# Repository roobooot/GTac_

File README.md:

# A Biomimetic Design of HeteroGeneous Tactile Sensor (GTac) Providing Normal and Shear Force Feedback

## General Introduction

This repo includes:

<ul>
  <li>the <a href="https://github.com/roobooot/GTac_/tree/main/software">code</a> 
    <ul>
      <li><a href="https://github.com/roobooot/GTac_/tree/main/software/arduino_lib">low-level controller</a> of GTac-Hand and GTac-Gripper</li>
      <li><a href="https://github.com/roobooot/GTac_/tree/main/software/GTac_Sensor">collecting data from GTac</a></li>
      <li>algorithms used for case study in papers, for instance, learning-based ECS recognition, handover controller, force-closed grasping, etc.</li>
    </ul>
</li>
  <li>the <a href="https://github.com/roobooot/GTac_/tree/main/hardware">hardware design</a>.
    <ul>
      <li><a href="https://github.com/roobooot/GTac_/tree/main/hardware/PCB%20design">PCB design</a> of GTac, reading-out boards, and the motors driving boards.</li>
      <li><a href="https://github.com/roobooot/GTac_/tree/main/hardware/Mechanical%20design">mechenical design</a> (CAD models)</li>
    </ul>
    </li>
</ul>

## Published Works

### GTac: A Biomimetic Tactile Sensor with Skin-like Heterogeneous Force Feedback for Robots

This paper is to introduce the design, fabrication methods, and force sensing principles of GTac.
For more information, please check out our paper below.

Z. Lu, X. Gao and H. Yu, "GTac: A Biomimetic Tactile Sensor With Skin-Like Heterogeneous Force Feedback for Robots," in IEEE Sensors Journal, vol. 22, no. 14, pp. 14491-14500, 15 July15, 2022, doi: 10.1109/JSEN.2022.3181128.

#### Video
<!------>
<p align="center">

</p>

## Contact Information
If you have any queries, do not hesitate to contact <a href="https://roobooot.github.io/">Zeyu Lu</a> (email: zeyu.lu@u.nus.edu).

## Acknowledge
This project is supervised by <a href="https://www.eng.nus.edu.sg/bme/staff/dr-yuhy/">Prof. Haoyong Yu</a> in <a href="https://wiki.nus.edu.sg/display/biorobotics/Biorobotics+Lab">Biorobotics Lab</a> @NUS.

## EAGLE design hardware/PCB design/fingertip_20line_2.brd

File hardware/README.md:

# Mechanical design
-Uncompress the zip

-open the hand_42_with_actua_box_v2.SLDASM in **Solidworks**. The design of GTac, and its integration can be found in the CAD model.
# PCB design
Using **EAGLE** to check out all the PCB design used to realize the GTac tactile sensing.

Image of sensing PCB:

Image of driving PCB:

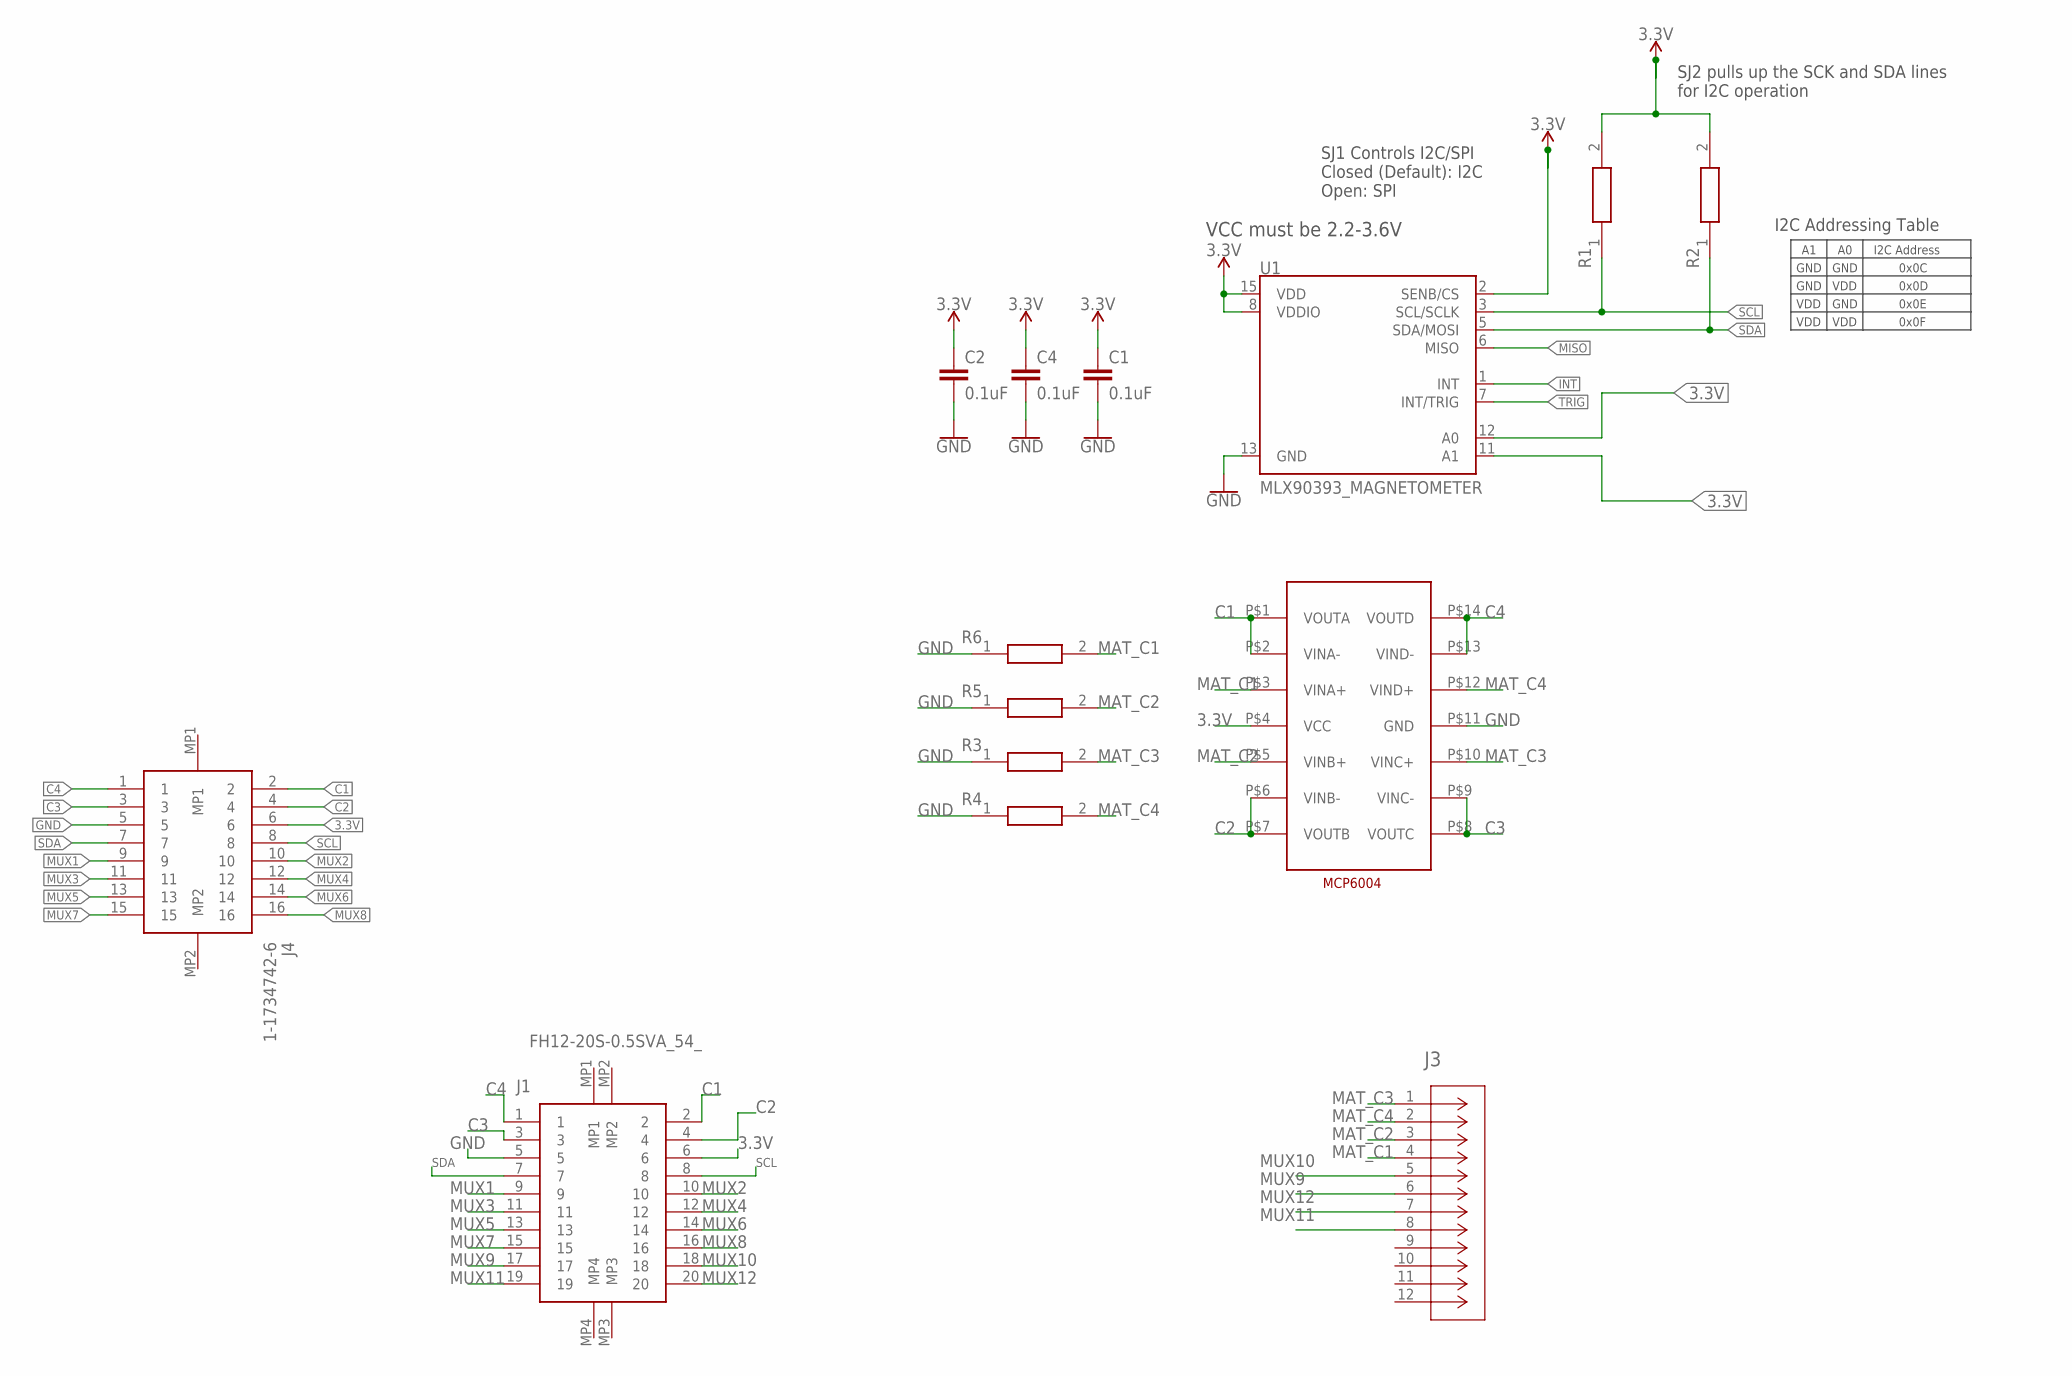
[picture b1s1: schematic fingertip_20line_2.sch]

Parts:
C1, C2, C4: 0.1uF; 0603
J1: FH12-20S-0.5SVA_54_; FH1220S05SVA54
J3: FH12-8S-1SV(55); CON8_1X8_DUTB1_HRS_HIR
J4: 1-1734742-6; 117347426
R1, R2, R3, R4, R5, R6: ERJ-S02J103X; RESC1005X40N
U1: MLX90393_MAGNETOMETER; QFN-16_WITH_AXIES
U$2: DECADE-MCP6004; DECADE-MCP6003

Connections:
3.3V: C1.1, C2.1, C4.1, J1.6, J4.6, R1.2, R2.2, U1.2 (SENB/CS), U1.8 (VDDIO), U1.11 (A1), U1.12 (A0), U1.15 (VDD), U$2.P$4 (VCC)
C1: J1.2, J4.2, U$2.P$1 (VOUTA), U$2.P$2 (VINA-)
C2: J1.4, J4.4, U$2.P$6 (VINB-), U$2.P$7 (VOUTB)
C3: J1.3, J4.3, U$2.P$8 (VOUTC), U$2.P$9 (VINC-)
C4: J1.1, J4.1, U$2.P$13 (VIND-), U$2.P$14 (VOUTD)
GND: C1.2, C2.2, C4.2, J1.5, J4.5, R3.1, R4.1, R5.1, R6.1, U1.13 (GND), U$2.P$11 (GND)
INT: U1.1 (INT)
MAT_C1: J3.4, R6.2, U$2.P$3 (VINA+)
MAT_C2: J3.3, R5.2, U$2.P$5 (VINB+)
MAT_C3: J3.1, R3.2, U$2.P$10 (VINC+)
MAT_C4: J3.2, R4.2, U$2.P$12 (VIND+)
MISO: U1.6 (MISO)
MUX1: J1.9, J4.9
MUX2: J1.10, J4.10
MUX3: J1.11, J4.11
MUX4: J1.12, J4.12
MUX5: J1.13, J4.13
MUX6: J1.14, J4.14
MUX7: J1.15, J4.15
MUX8: J1.16, J4.16
MUX9: J1.17, J3.6
MUX10: J1.18, J3.5
MUX11: J1.19, J3.8
MUX12: J1.20, J3.7
SCL: J1.8, J4.8, R1.1, U1.3 (SCL/SCLK)
SDA: J1.7, J4.7, R2.1, U1.5 (SDA/MOSI)
TRIG: U1.7 (INT/TRIG)

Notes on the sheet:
SJ2 pulls up the SCK and SDA lines for I2C operation
VCC must be 2.2-3.6V
SJ1 Controls I2C/SPI Closed (Default): I2C Open: SPI
I2C Address
0x0C
0x0D
0x0E
0x0F
GND
VDD
I2C Addressing Table

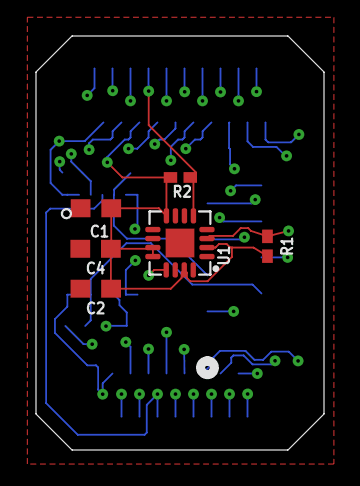
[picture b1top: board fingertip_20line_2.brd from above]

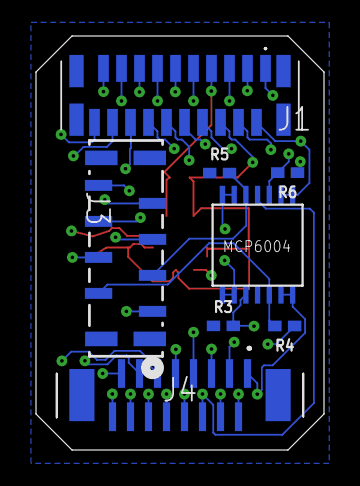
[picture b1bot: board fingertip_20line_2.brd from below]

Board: 4 copper layers, 16.0 x 23.0 mm, 14 parts (8 on the bottom side), 24 nets.

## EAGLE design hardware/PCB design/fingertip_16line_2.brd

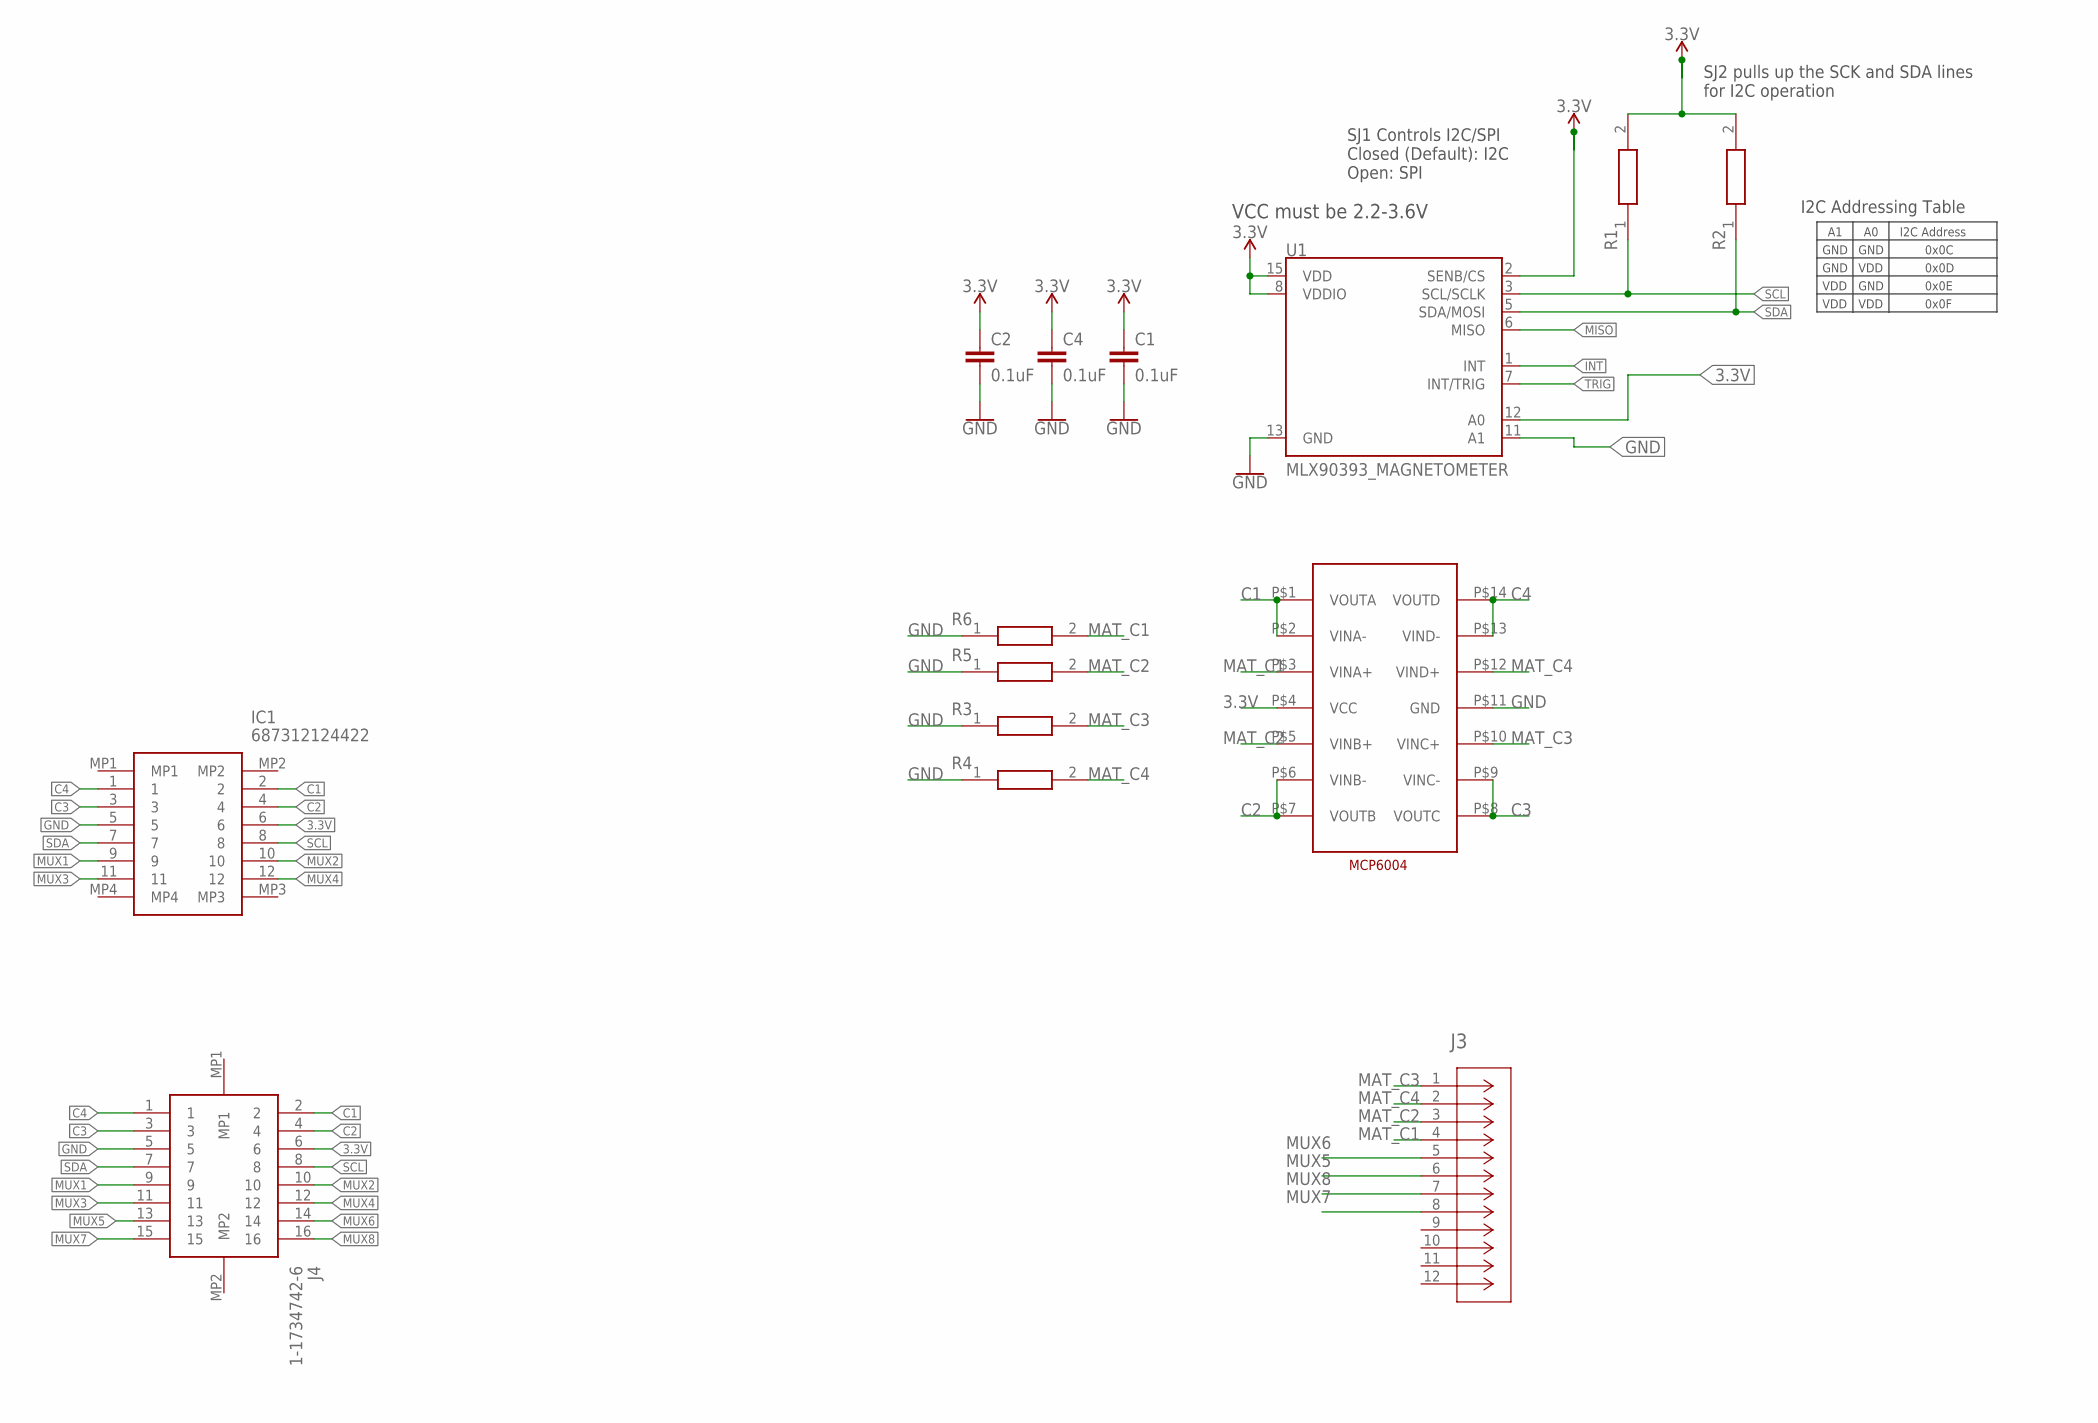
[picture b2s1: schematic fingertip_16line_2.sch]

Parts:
C1, C2, C4: 0.1uF; 0402
IC1: 687312124422
J3: FH12-8S-1SV(55); CON8_1X8_DUTB1_HRS_HIR
J4: 1-1734742-6; 117347426
R1, R2, R3, R4, R5, R6: ERJ-S02J103X; RESC1005X40N
U1: MLX90393_MAGNETOMETER; QFN-16_WITH_AXIES
U$2: DECADE-MCP6004; DECADE-MCP6003

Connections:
3.3V: C1.1, C2.1, C4.1, IC1.6, J4.6, R1.2, R2.2, U1.2 (SENB/CS), U1.8 (VDDIO), U1.12 (A0), U1.15 (VDD), U$2.P$4 (VCC)
C1: IC1.2, J4.2, U$2.P$1 (VOUTA), U$2.P$2 (VINA-)
C2: IC1.4, J4.4, U$2.P$6 (VINB-), U$2.P$7 (VOUTB)
C3: IC1.3, J4.3, U$2.P$8 (VOUTC), U$2.P$9 (VINC-)
C4: IC1.1, J4.1, U$2.P$13 (VIND-), U$2.P$14 (VOUTD)
GND: C1.2, C2.2, C4.2, IC1.5, J4.5, R3.1, R4.1, R5.1, R6.1, U1.11 (A1), U1.13 (GND), U$2.P$11 (GND)
INT: U1.1 (INT)
MAT_C1: J3.4, R6.2, U$2.P$3 (VINA+)
MAT_C2: J3.3, R5.2, U$2.P$5 (VINB+)
MAT_C3: J3.1, R3.2, U$2.P$10 (VINC+)
MAT_C4: J3.2, R4.2, U$2.P$12 (VIND+)
MISO: U1.6 (MISO)
MUX1: IC1.9, J4.9
MUX2: IC1.10, J4.10
MUX3: IC1.11, J4.11
MUX4: IC1.12, J4.12
MUX5: J3.6, J4.13
MUX6: J3.5, J4.14
MUX7: J3.8, J4.15
MUX8: J3.7, J4.16
SCL: IC1.8, J4.8, R1.1, U1.3 (SCL/SCLK)
SDA: IC1.7, J4.7, R2.1, U1.5 (SDA/MOSI)
TRIG: U1.7 (INT/TRIG)

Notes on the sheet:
SJ2 pulls up the SCK and SDA lines for I2C operation
VCC must be 2.2-3.6V
SJ1 Controls I2C/SPI Closed (Default): I2C Open: SPI
I2C Address
0x0C
0x0D
0x0E
0x0F
GND
VDD
I2C Addressing Table

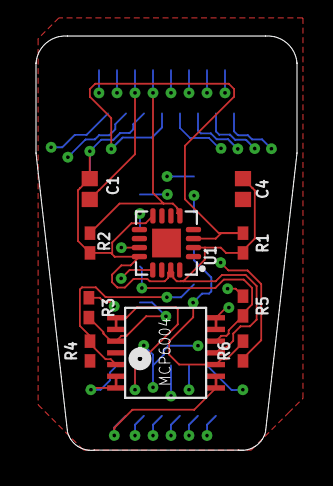
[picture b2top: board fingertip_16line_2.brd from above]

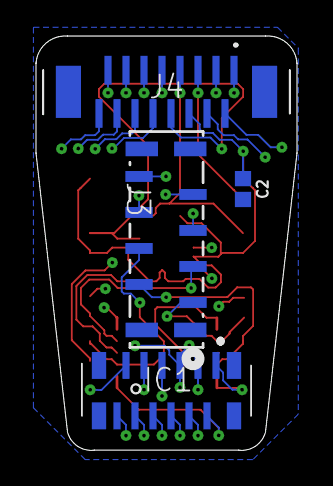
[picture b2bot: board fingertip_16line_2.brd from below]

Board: 4 copper layers, 14.5 x 23.0 mm, 14 parts (4 on the bottom side), 20 nets.

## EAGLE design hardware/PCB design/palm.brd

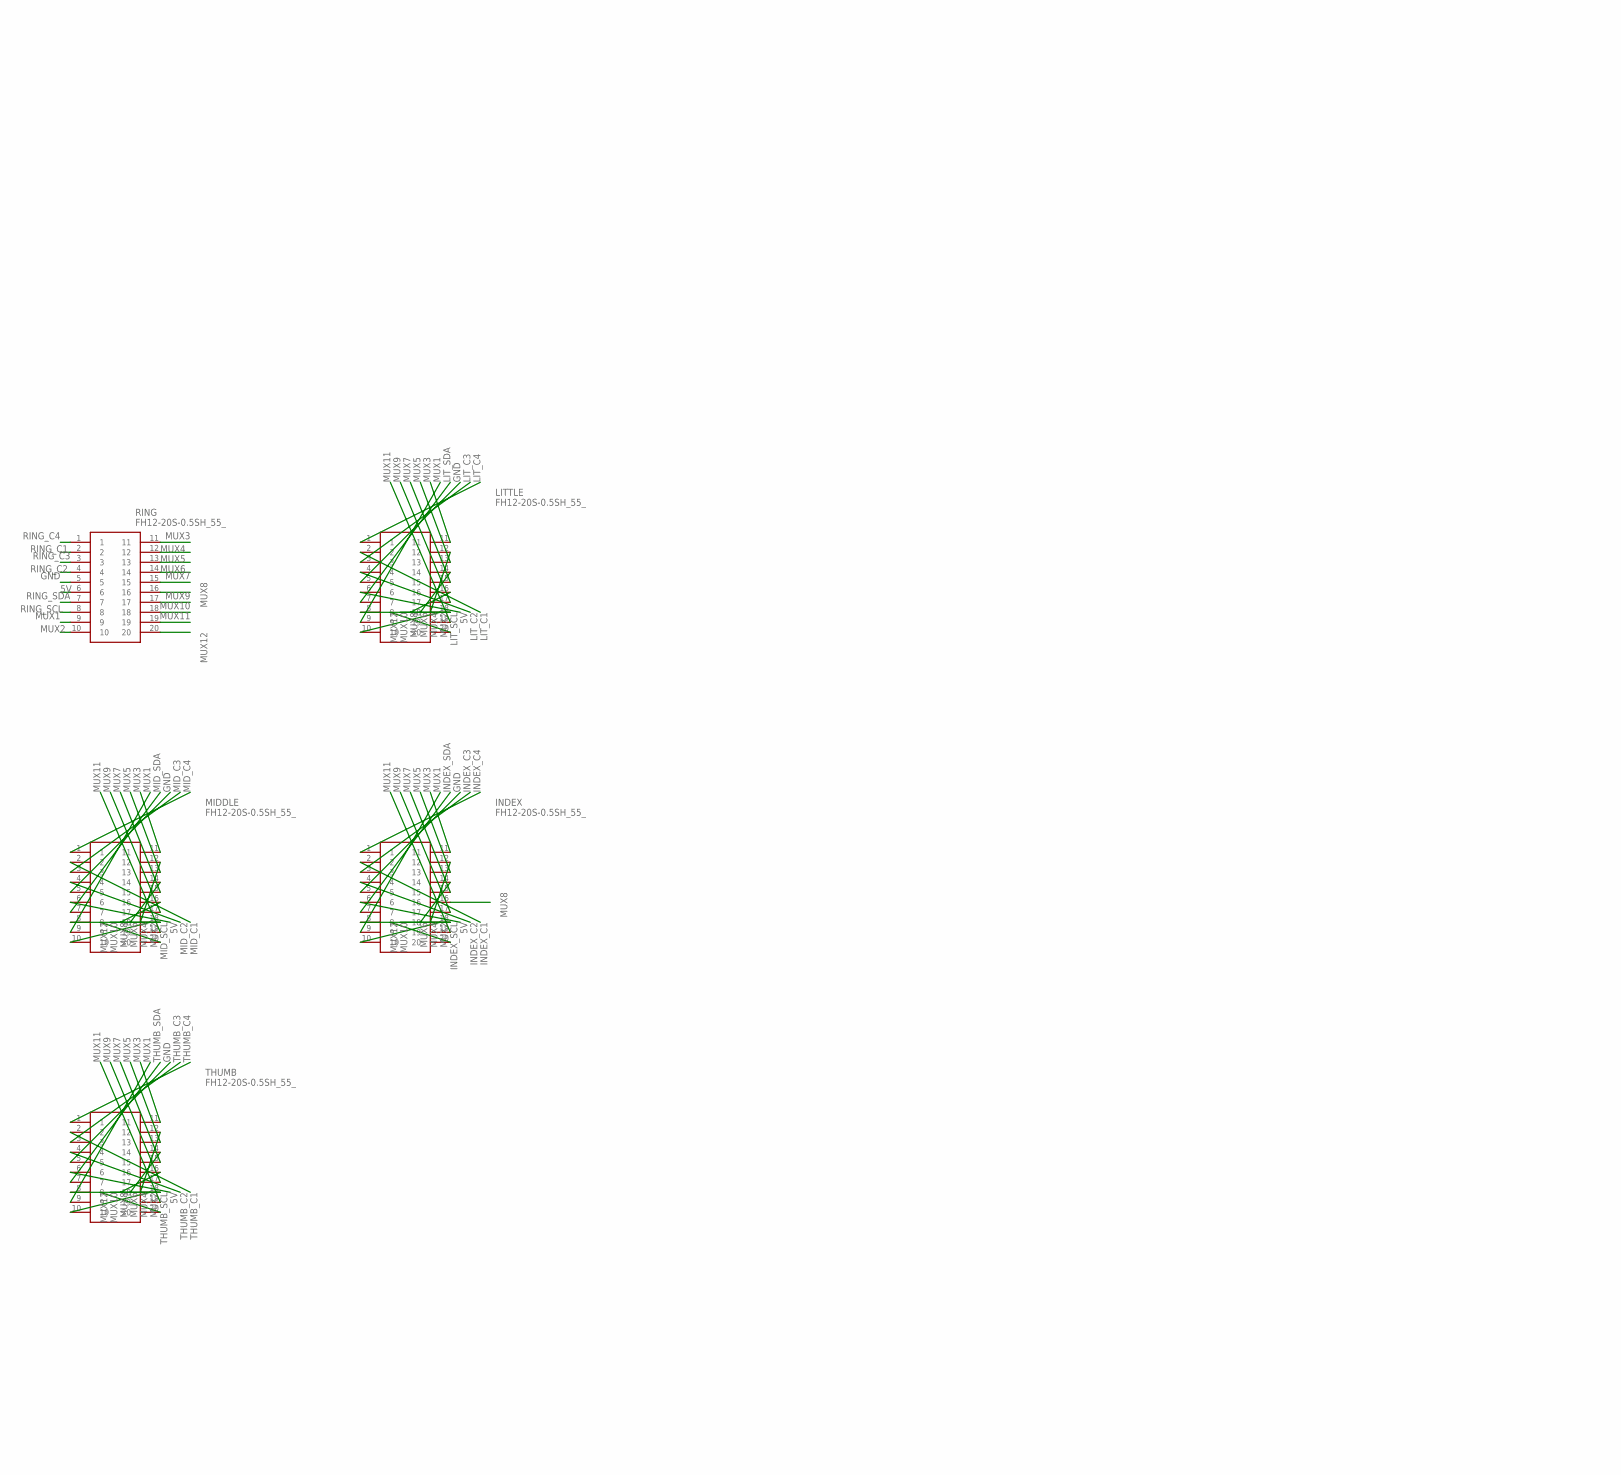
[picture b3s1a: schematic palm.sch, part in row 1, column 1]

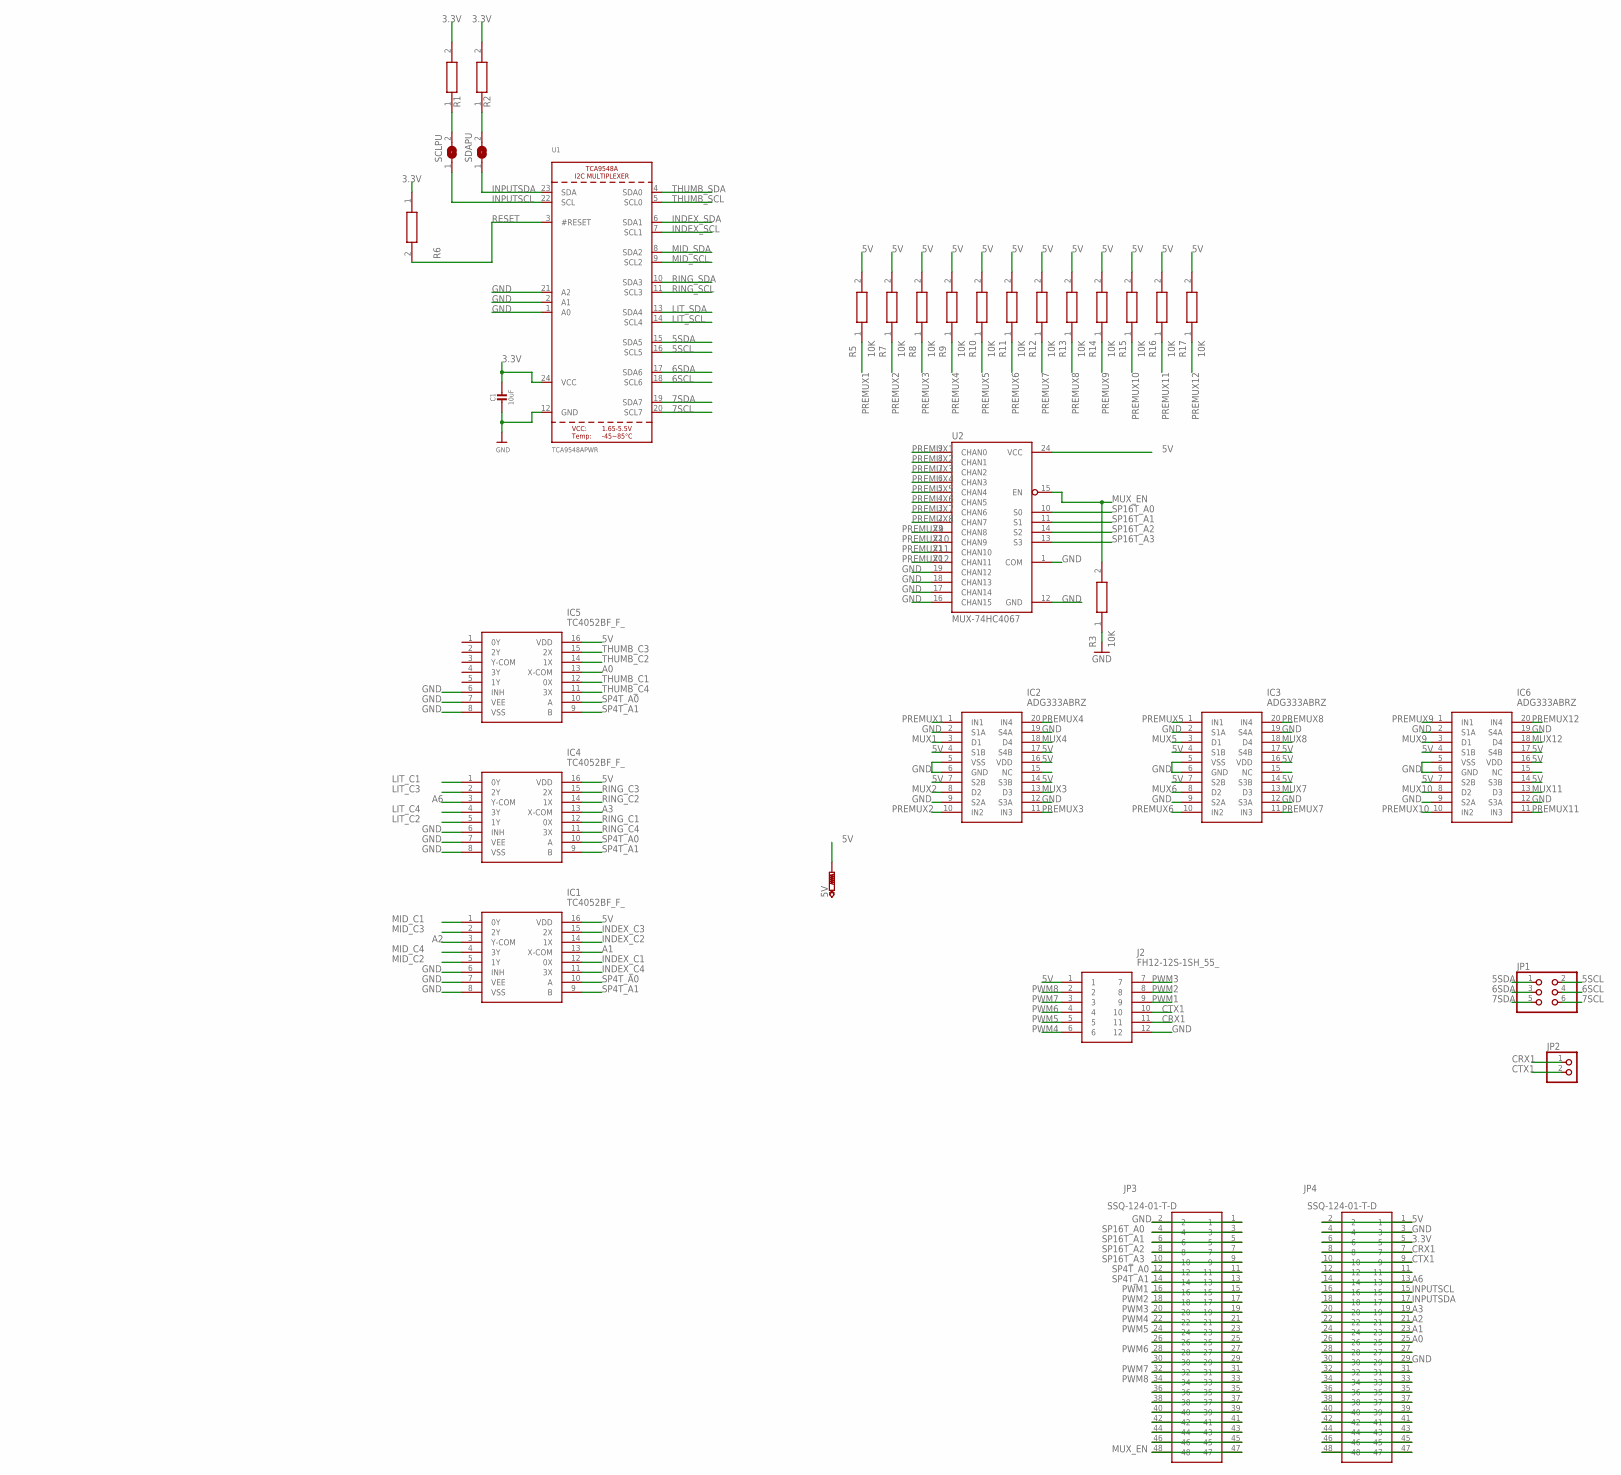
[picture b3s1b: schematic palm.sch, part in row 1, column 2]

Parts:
5V: PTR1B1,27; B1,27
C1: 10uF; 0805-NO
IC1, IC4, IC5: TC4052BF_F_; SOIC127P780X190-16N
IC2, IC3, IC6: ADG333ABRZ; SOIC127P1032X265-20N
INDEX: FH12-20S-0.5SH_55_; FH12-20S-0.5SH(55)
J2: FH12-12S-1SH_55_; FH12-12S-1SH(55)
JP1: PINHD-2X3; 2X03
JP2: PINHD-1X2; 1X02
JP3, JP4: SSQ-124-01-T-D; SSQ-124-XX-YYY
LITTLE: FH12-20S-0.5SH_55_; FH12-20S-0.5SH(55)
MIDDLE: FH12-20S-0.5SH_55_; FH12-20S-0.5SH(55)
R1, R2, R6: ERJ-S02J103X; RESC1005X40N
R3, R5, R7, R8, R9, R10, R11, R12, R13, R14, R15, R16, R17: 10K; RESC1005X40N
RING: FH12-20S-0.5SH_55_; FH12-20S-0.5SH(55)
SCLPU: SOLDERJUMPERCLOSED; SOLDERJUMPER_CLOSEDWIRE
SDAPU: SOLDERJUMPERCLOSED; SOLDERJUMPER_CLOSEDWIRE
THUMB: FH12-20S-0.5SH_55_; FH12-20S-0.5SH(55)
U1: TCA9548APWR; TSSOP24
U2: MUX-74HC4067; SSOP24

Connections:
3.3V: C1.1, JP4.5, JP4.6, R1.2, R2.2, R6.1, U1.24 (VCC)
5SCL: JP1.2, U1.16 (SCL5)
5SDA: JP1.1, U1.15 (SDA5)
5V: 5V.TP, IC1.16 (VDD), IC2.4 (S1B), IC2.7 (S2B), IC2.14 (S3B), IC2.16 (VDD), IC2.17 (S4B), IC3.4 (S1B), IC3.7 (S2B), IC3.14 (S3B), IC3.16 (VDD), IC3.17 (S4B), IC4.16 (VDD), IC5.16 (VDD), IC6.4 (S1B), IC6.7 (S2B), IC6.14 (S3B), IC6.16 (VDD), IC6.17 (S4B), INDEX.6, J2.1, JP4.1, JP4.2, LITTLE.6, MIDDLE.6, R5.2, R7.2, R8.2, R9.2, R10.2, R11.2, R12.2, R13.2, R14.2, R15.2, R16.2, R17.2, RING.6, THUMB.6, U2.24 (VCC)
6SCL: JP1.4, U1.18 (SCL6)
6SDA: JP1.3, U1.17 (SDA6)
7SCL: JP1.6, U1.20 (SCL7)
7SDA: JP1.5, U1.19 (SDA7)
A0: IC5.13 (X-COM), JP4.25, JP4.26
A1: IC1.13 (X-COM), JP4.23, JP4.24
A2: IC1.3 (Y-COM), JP4.21, JP4.22
A3: IC4.13 (X-COM), JP4.19, JP4.20
A6: IC4.3 (Y-COM), JP4.13, JP4.14
CRX1: J2.11, JP2.1, JP4.7, JP4.8
CTX1: J2.10, JP2.2, JP4.9, JP4.10
GND: C1.2, IC1.6 (INH), IC1.7 (VEE), IC1.8 (VSS), IC2.2 (S1A), IC2.5 (VSS), IC2.6 (GND), IC2.9 (S2A), IC2.12 (S3A), IC2.19 (S4A), IC3.2 (S1A), IC3.5 (VSS), IC3.6 (GND), IC3.9 (S2A), IC3.12 (S3A), IC3.19 (S4A), IC4.6 (INH), IC4.7 (VEE), IC4.8 (VSS), IC5.6 (INH), IC5.7 (VEE), IC5.8 (VSS), IC6.2 (S1A), IC6.5 (VSS), IC6.6 (GND), IC6.9 (S2A), IC6.12 (S3A), IC6.19 (S4A), INDEX.5, J2.12, JP3.1, JP3.2, JP4.3, JP4.4, JP4.29, JP4.30, LITTLE.5, MIDDLE.5, R3.1, RING.5, THUMB.5, U1.1 (A0), U1.2 (A1), U1.12 (GND), U1.21 (A2), U2.1 (COM), U2.12 (GND), U2.16 (CHAN15), U2.17 (CHAN14), U2.18 (CHAN13), U2.19 (CHAN12)
INDEX_C1: IC1.12 (0X), INDEX.2
INDEX_C2: IC1.14 (1X), INDEX.4
INDEX_C3: IC1.15 (2X), INDEX.3
INDEX_C4: IC1.11 (3X), INDEX.1
INDEX_SCL: INDEX.8, U1.7 (SCL1)
INDEX_SDA: INDEX.7, U1.6 (SDA1)
INPUTSCL: JP4.15, JP4.16, SCLPU.1, U1.22 (SCL)
INPUTSDA: JP4.17, JP4.18, SDAPU.1, U1.23 (SDA)
LIT_C1: IC4.1 (0Y), LITTLE.2
LIT_C2: IC4.5 (1Y), LITTLE.4
LIT_C3: IC4.2 (2Y), LITTLE.3
LIT_C4: IC4.4 (3Y), LITTLE.1
LIT_SCL: LITTLE.8, U1.14 (SCL4)
LIT_SDA: LITTLE.7, U1.13 (SDA4)
MID_C1: IC1.1 (0Y), MIDDLE.2
MID_C2: IC1.5 (1Y), MIDDLE.4
MID_C3: IC1.2 (2Y), MIDDLE.3
MID_C4: IC1.4 (3Y), MIDDLE.1
MID_SCL: MIDDLE.8, U1.9 (SCL2)
MID_SDA: MIDDLE.7, U1.8 (SDA2)
MUX1: IC2.3 (D1), INDEX.9, LITTLE.9, MIDDLE.9, RING.9, THUMB.9
MUX2: IC2.8 (D2), INDEX.10, LITTLE.10, MIDDLE.10, RING.10, THUMB.10
MUX3: IC2.13 (D3), INDEX.11, LITTLE.11, MIDDLE.11, RING.11, THUMB.11
MUX4: IC2.18 (D4), INDEX.12, LITTLE.12, MIDDLE.12, RING.12, THUMB.12
MUX5: IC3.3 (D1), INDEX.13, LITTLE.13, MIDDLE.13, RING.13, THUMB.13
MUX6: IC3.8 (D2), INDEX.14, LITTLE.14, MIDDLE.14, RING.14, THUMB.14
MUX7: IC3.13 (D3), INDEX.15, LITTLE.15, MIDDLE.15, RING.15, THUMB.15
MUX8: IC3.18 (D4), INDEX.16, LITTLE.16, MIDDLE.16, RING.16, THUMB.16
MUX9: IC6.3 (D1), INDEX.17, LITTLE.17, MIDDLE.17, RING.17, THUMB.17
MUX10: IC6.8 (D2), INDEX.18, LITTLE.18, MIDDLE.18, RING.18, THUMB.18
MUX11: IC6.13 (D3), INDEX.19, LITTLE.19, MIDDLE.19, RING.19, THUMB.19
MUX12: IC6.18 (D4), INDEX.20, LITTLE.20, MIDDLE.20, RING.20, THUMB.20
MUX_EN: JP3.47, JP3.48, R3.2, U2.15 (EN)
unnamed: R1.1, SCLPU.2
unnamed: R2.1, SDAPU.2
unnamed: JP3.25, JP3.26
unnamed: JP3.29, JP3.30
unnamed: JP3.35, JP3.36
unnamed: JP3.37, JP3.38
unnamed: JP3.39, JP3.40
unnamed: JP3.41, JP3.42
unnamed: JP3.43, JP3.44
unnamed: JP3.45, JP3.46
unnamed: JP4.11, JP4.12
unnamed: JP4.27, JP4.28
unnamed: JP4.31, JP4.32
unnamed: JP4.33, JP4.34
unnamed: JP4.35, JP4.36
unnamed: JP4.37, JP4.38
unnamed: JP4.39, JP4.40
unnamed: JP4.41, JP4.42
unnamed: JP4.43, JP4.44
unnamed: JP4.45, JP4.46
unnamed: JP4.47, JP4.48
PREMUX1: IC2.1 (IN1), R5.1, U2.9 (CHAN0)
PREMUX2: IC2.10 (IN2), R7.1, U2.8 (CHAN1)
PREMUX3: IC2.11 (IN3), R8.1, U2.7 (CHAN2)
PREMUX4: IC2.20 (IN4), R9.1, U2.6 (CHAN3)
PREMUX5: IC3.1 (IN1), R10.1, U2.5 (CHAN4)
PREMUX6: IC3.10 (IN2), R11.1, U2.4 (CHAN5)
PREMUX7: IC3.11 (IN3), R12.1, U2.3 (CHAN6)
PREMUX8: IC3.20 (IN4), R13.1, U2.2 (CHAN7)
PREMUX9: IC6.1 (IN1), R14.1, U2.23 (CHAN8)
PREMUX10: IC6.10 (IN2), R15.1, U2.22 (CHAN9)
PREMUX11: IC6.11 (IN3), R16.1, U2.21 (CHAN10)
PREMUX12: IC6.20 (IN4), R17.1, U2.20 (CHAN11)
PWM1: J2.9, JP3.15, JP3.16
PWM2: J2.8, JP3.17, JP3.18
PWM3: J2.7, JP3.19, JP3.20
PWM4: J2.6, JP3.21, JP3.22
PWM5: J2.5, JP3.23, JP3.24
PWM6: J2.4, JP3.27, JP3.28
PWM7: J2.3, JP3.31, JP3.32
PWM8: J2.2, JP3.33, JP3.34
RESET: R6.2, U1.3 (#RESET)
RING_C1: IC4.12 (0X), RING.2
RING_C2: IC4.14 (1X), RING.4
RING_C3: IC4.15 (2X), RING.3
RING_C4: IC4.11 (3X), RING.1
RING_SCL: RING.8, U1.11 (SCL3)
RING_SDA: RING.7, U1.10 (SDA3)
SP4T_A0: IC1.10 (A), IC4.10 (A), IC5.10 (A), JP3.11, JP3.12
SP4T_A1: IC1.9 (B), IC4.9 (B), IC5.9 (B), JP3.13, JP3.14
SP16T_A0: JP3.3, JP3.4, U2.10 (S0)
SP16T_A1: JP3.5, JP3.6, U2.11 (S1)
SP16T_A2: JP3.7, JP3.8, U2.14 (S2)
SP16T_A3: JP3.9, JP3.10, U2.13 (S3)
THUMB_C1: IC5.12 (0X), THUMB.2
THUMB_C2: IC5.14 (1X), THUMB.4
THUMB_C3: IC5.15 (2X), THUMB.3
THUMB_C4: IC5.11 (3X), THUMB.1
THUMB_SCL: THUMB.8, U1.5 (SCL0)
THUMB_SDA: THUMB.7, U1.4 (SDA0)

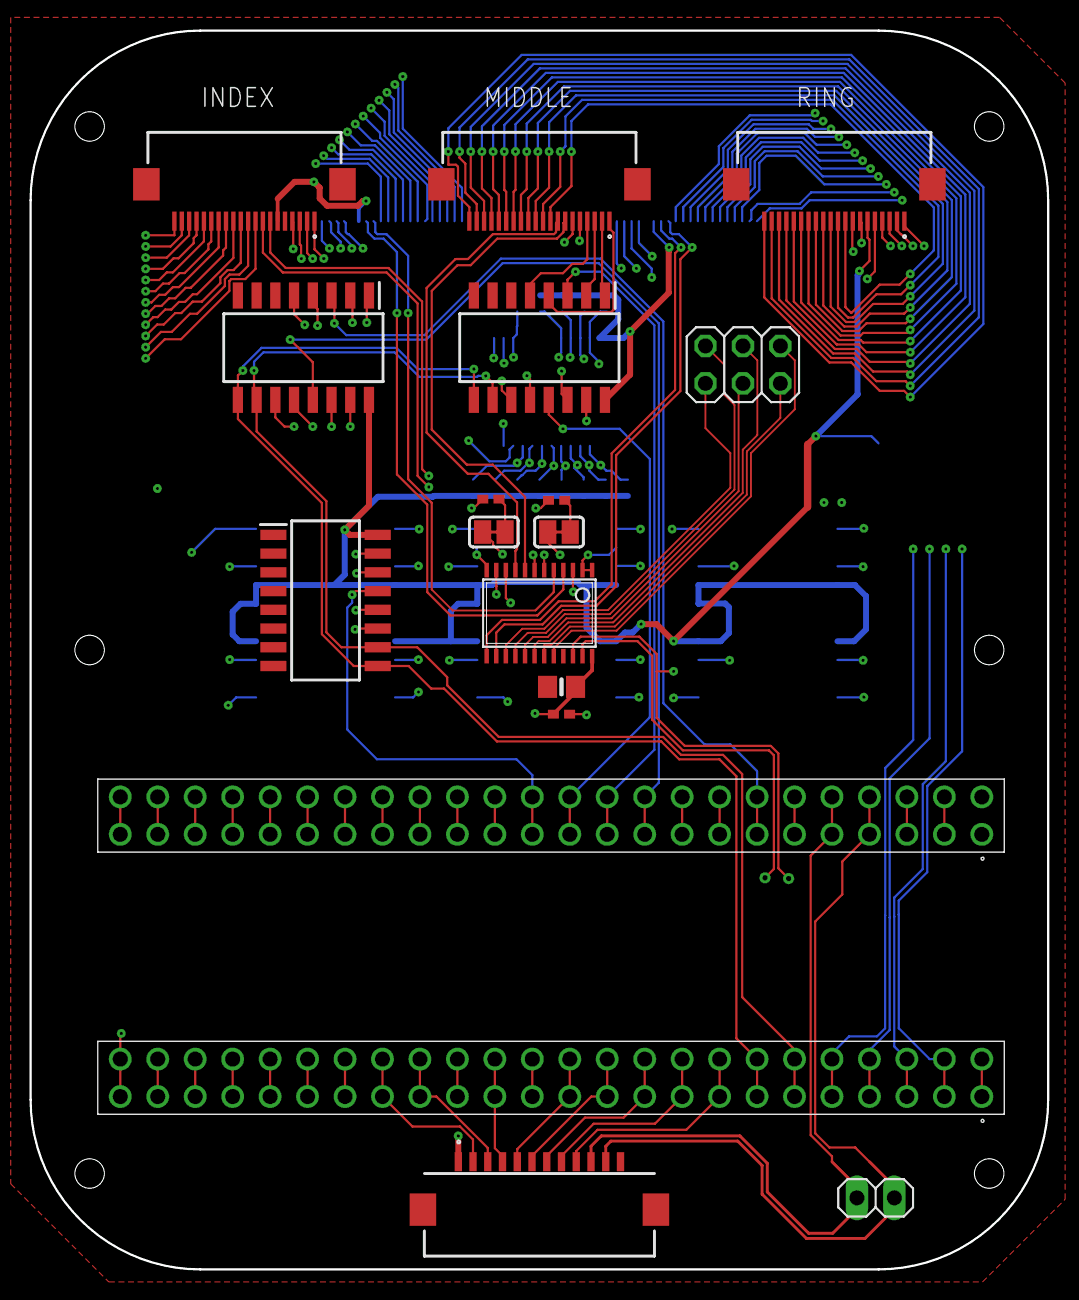
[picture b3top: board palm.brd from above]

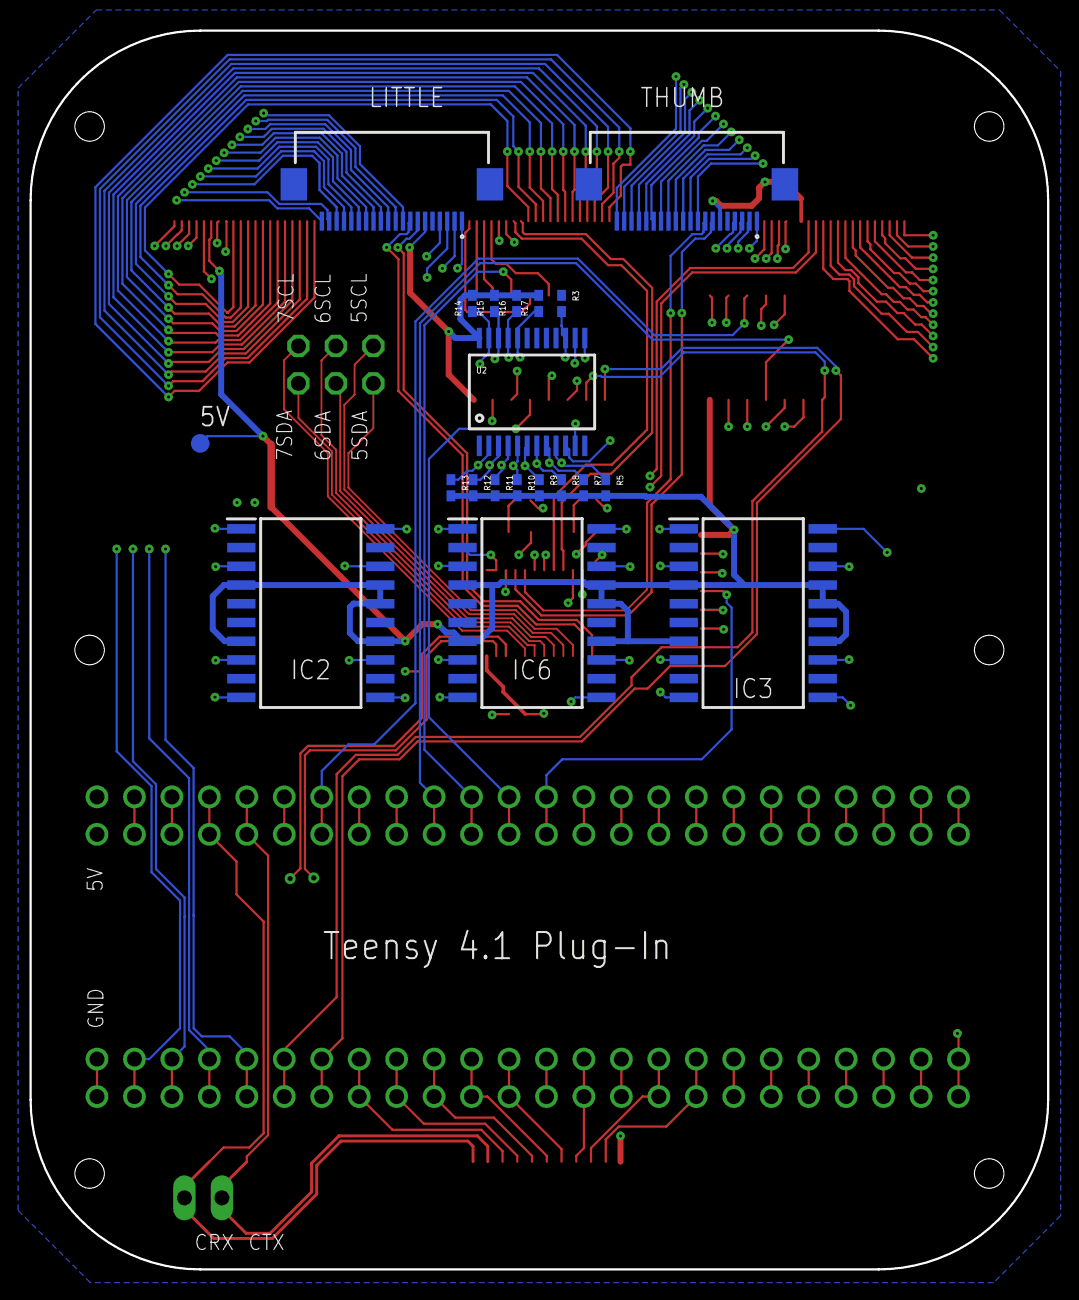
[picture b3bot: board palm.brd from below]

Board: 4 copper layers, 69.0 x 84.0 mm, 38 parts (20 on the bottom side), 109 nets.

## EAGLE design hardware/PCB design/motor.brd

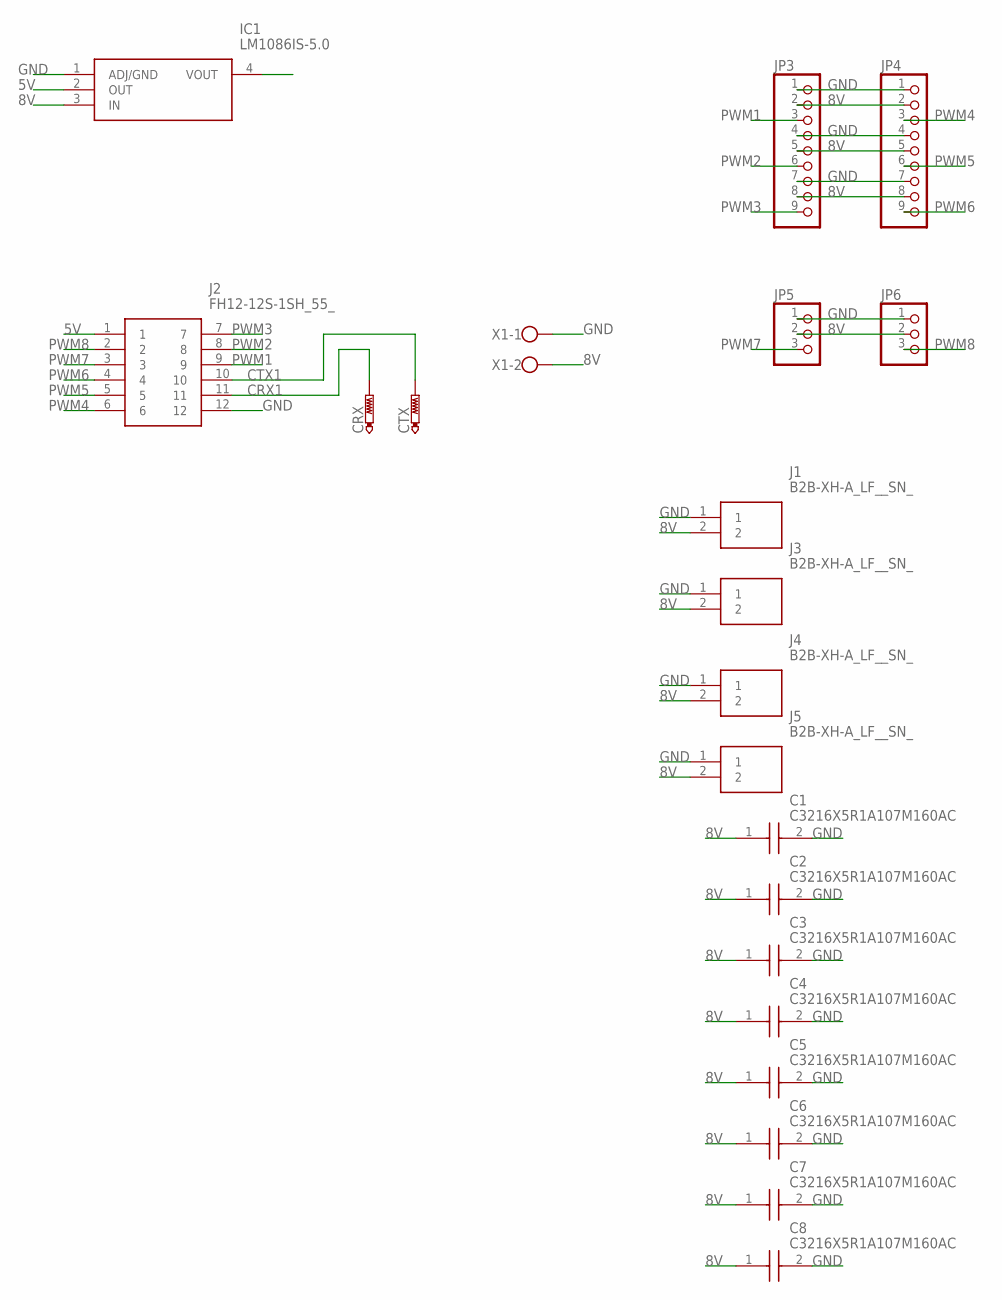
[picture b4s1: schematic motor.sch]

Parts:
C1, C2, C3, C4, C5, C6, C7, C8: C3216X5R1A107M160AC; CAPC3216X180N
CRX: PTR1TP20R; TP20R
CTX: PTR1TP20SQ; TP20SQ
IC1: LM1086IS-5.0; TO254P1435X457-4N
J1, J3, J4, J5: B2B-XH-A_LF__SN_; SHDR2W64P0X250_1X2_740X575X700
J2: FH12-12S-1SH_55_; FH12-12S-1SH(55)
JP3, JP4: PINHD-1X9; 1X09
JP5, JP6: PINHD-1X3; 1X03
X1: W237-102

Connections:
5V: IC1.2 (OUT), J2.1
8V: C1.1, C2.1, C3.1, C4.1, C5.1, C6.1, C7.1, C8.1, IC1.3 (IN), J1.2, J3.2, J4.2, J5.2, JP3.2, JP3.5, JP3.8, JP4.2, JP4.5, JP4.8, JP5.2, JP6.2, X1.2
CRX1: CRX.TP, J2.11
CTX1: CTX.TP, J2.10
GND: C1.2, C2.2, C3.2, C4.2, C5.2, C6.2, C7.2, C8.2, IC1.1 (ADJ/GND), J1.1, J2.12, J3.1, J4.1, J5.1, JP3.1, JP3.4, JP3.7, JP4.1, JP4.4, JP4.7, JP5.1, JP6.1, X1.1
PWM1: J2.9, JP3.3
PWM2: J2.8, JP3.6
PWM3: J2.7, JP3.9
PWM4: J2.6, JP4.3
PWM5: J2.5, JP4.6
PWM6: J2.4, JP4.9
PWM7: J2.3, JP5.3
PWM8: J2.2, JP6.3

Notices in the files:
parts and their libraries:
SparkFun-Capacitors: Licensing: Creative Commons ShareAlike 4.0 International - https://creativecommons.org/licenses/by-sa/4.0
COPYRIGHT: Copyright (C) 2018 Accelerated Designs. All rights reserved
